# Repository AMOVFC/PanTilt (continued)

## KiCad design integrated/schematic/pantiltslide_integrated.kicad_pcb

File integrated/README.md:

# Integrated Controller — All Components Soldered (PCBWay assembly)

Fully-integrated version of the [4-axis final rig](../pantiltslide/pantiltslide_full.kicad_sch): every IC soldered directly to the board instead of socketed breakout modules, sized for a PCBWay turnkey assembly order. Companion to `pantiltslide/pantiltslide_full.kicad_sch` (the carrier-board version) — that board still exists and is untouched.

**Status: schematic + PCB placement complete and verified. Not routed, so not yet ready for fab.** See "PCB status" below.

## What's integrated vs. what stays a connector

| Was a socket/module in the carrier board | Now | Why |
|---|---|---|
| ESP32-S3 DevKitC (22-pin sockets) | ESP32-S3-WROOM-1-N16R8 module, soldered | Module has its own certified antenna/crystal — no RF layout risk |
| 4× TMC2209 stepstick sockets | 4× TMC2209-LA (QFN28), full app circuit | Standard Trinamic reference design, verified against datasheet |
| 2× AS5600 breakout connectors | Still connectors — now 4-pin JST XH (`J7`, `J8`) | An AS5600 needs a <3 mm air gap to a magnet on the rotating shaft, so it can't sit on the controller board. Off-the-shelf AS5600 breakout modules stay at the pan/tilt joints, wired back over XH. |
| TCA9548A breakout connector | TCA9548A (TSSOP24), soldered | Standard I2C mux app circuit |
| — (no regulation existed) | 24V→5V buck (LM2596S-5) → 5V→3.3V LDO (AMS1117-3.3) | Carrier board had no onboard regulation at all — this is genuinely new |
| — | USB-C connector, native USB on the S3 | Bench programming/power without the 24V rail connected |
| SSD1306 OLED connector | **Unchanged** — still a connector | It's a glass panel, not something an assembly house places |
| Motor/encoder/limit-switch connectors | Still connectors, now **JST XH** | Polarised and latching — see the Connectors table below |

All part choices (TMC2209-LA, ESP32-S3-WROOM-1, AS5600, TCA9548APWR, LM2596S-5, AMS1117-3.3) are mainstream, high-volume parts — good candidates for PCBWay's turnkey sourcing, not exotic.

## Pin map

Identical to the final rig's — see the main [README pin map](../README.md#pin-map). This schematic was built directly from that table, not from the carrier board's connectors (which had drifted: J33–J36 in the carrier board are leftover keyframe-button connectors that don't correspond to anything in the current firmware's pin map or the "trigger a shot over serial" design described in the main README. They're intentionally not carried over here.)

## Verification status

**ERC: 0 violations. Netlist verified pin-by-pin against the intended design.**

Nets use **global labels**, matching the convention in `pantiltslide_full.kicad_sch`.

### Sheet organisation

Drawn on an A1 sheet in four labelled blocks — power in / regulation, MCU + USB, I2C mux + off-board connectors, and the four TMC2209 drivers in a 2x2 grid.

Power rails are drawn as **GND / +3V3 / +5V / +24V symbols**, not text labels. 158 of the 331 net connections on this sheet are power (90 of them GND alone); as labels they buried the actual signal flow in a wall of repeated text. Only real signals carry label text now — 173 labels instead of 331.

### What was wrong in the first two drafts, and the actual root cause

KiCad **negates Y** when it places a library symbol: a pin at library coordinate `(lx, ly)` lands at screen `(sym_x + lx, sym_y − ly)`. The generator was *adding* `ly`, which mirrors every symbol vertically. Consequences:

- On vertically symmetric parts (resistors, capacitors) the label still landed on a real pin — but **the wrong one**, silently swapping pin 1 and pin 2.
- On asymmetric ICs (TMC2209, TCA9548A, ESP32-S3, USB-C) labels landed in empty space, so those pins read as unconnected.

I had earlier blamed this on `kicad-cli` being buggy. That was wrong — it was this bug, and the tool was reporting it accurately. Ground truth was confirmed from this repo's own `pantiltslide_full.kicad_sch`: J21 placed at `(430,40)` has pin 1 at `y=37.46` (`40 − 2.54`) and pin 4 at `y=45.08` (`40 − (−5.08)`).

Also fixed along the way:
- Net labels had no wire attaching them to pins (label-on-pin is not a connection mechanism in KiCad) — every pin now has a real drawn wire stub to its label.
- Everything snapped to the 1.27 mm connection grid.
- **USB-C `B6`/`B7` were left unconnected.** These are *not* redundant stacked pins — D+ and D− appear on both sides of a Type-C connector so the plug works either way up. Tying only the A-side would have produced a port that works in one orientation and is dead when flipped. `A6+B6` and `A7+B7` are now tied.

### How it was verified

- `kicad-cli sch erc` → **0 violations**.
- Netlist exported and diffed against the intended design: **75/80 nets byte-identical**. The 5 differences were each confirmed benign — `#PWR`/`#FLG` symbols are virtual and by design never exported as components, and the USB-C `A12/B1/B12` (GND) and `A9/B4/B9` (VBUS) pads share exact coordinates with `A1`/`A4`, so KiCad correctly folds them into those nets.
- Spot-checked against the firmware pin map: `GPIO4 → U4.STEP`, `GPIO10 →` all four driver `EN` pins, `TMC_UART` = 1 kΩ series resistor + `IO41` + all four `PDN_UART` pins, `I2C_PAN_SDA` = pull-up + mux channel 0 + AS5600 `SDA`.

The two hand-authored symbols (AS5600, ESP32-S3-WROOM-1) ship as an editable `New_Library.kicad_sym` with a `sym-lib-table`, so they open normally in the Symbol Editor rather than existing only as embedded copies.

Layout still needs a human pass — see "PCB status" below.

## PCB status

One board: `schematic/pantiltslide_integrated.*`

| | |
|---|---|
| Size | 150 × 120 mm |
| Layers | 4 (F.Cu / GND / 3V3 / B.Cu) |
| Footprints | 80 |
| ERC | **0** |
| Schematic parity | **0** |
| DRC (excl. routing) | 7 (4 cosmetic silk, 2 antenna-overhang silk, 1 benign keepout layer-set) |
| **Routing** | **not routed — 253 ratsnest connections** |

**The board is placed and netted, not routed.** Every pad carries its correct net so the ratsnest is complete and correct, but no copper tracks exist yet. Routing is the next step — either by hand in KiCad, or by exporting Specctra DSN (File → Export → Specctra DSN, GUI only — `kicad-cli` has no DSN export) and running Freerouting.

## Connectors

Everything that leaves the board is **JST XH** — polarised so a harness can't be plugged in backwards, latching so it won't shake loose on a moving rig, and rated 3 A/contact (comfortably above the TMC2209's 2 A RMS ceiling). The sole exception is the 24 V input, which keeps a screw terminal for bare supply leads.

| Ref | Function | Connector |
|---|---|---|
| `J1` | 24 V motor supply in | **Screw terminal**, 5.0 mm |
| `J2` | USB-C (power + programming) | USB-C receptacle |
| `J3`–`J6` | Motors: slide / pan / tilt / Z | XH 4-pin |
| `J7`, `J8` | AS5600 modules: pan / tilt | XH 4-pin — `3V3, GND, SDA, SCL` |
| `J9` | SSD1306 OLED | XH 4-pin — `3V3, GND, SDA, SCL` |
| `J10`, `J11` | Encoders: jog / angle | XH 4-pin — `A, B, push, GND` |
| `J12`–`J14` | Limit switches: slide min / max / Z home | XH 2-pin |

Every connector prints its **function on the front silkscreen** (`Motor_Tilt`, `AS5600_Pan`, `Limit_Z_Home` …) directly below its reference designator, so the board can be wired without the schematic to hand. pcbnew's default leaves the Value field hidden and on `F.Fab`, which is a documentation layer and never reaches the physical board — both were changed for all 14 connectors, and the placement packer reserves vertical room for the two text rows.

The AS5600s are **off-the-shelf breakout modules** mounted at the pan and tilt joints, not parts on this board — the sensor has to sit within a few mm of a diametrically-magnetised magnet on the rotating shaft. Two things to check on whichever module you buy:

- **Pin order.** `J7`/`J8` are wired `1=3V3, 2=GND, 3=SDA, 4=SCL`. Most AS5600 breakouts use that order, but confirm before crimping — a swapped 3V3/GND will destroy the module.
- **The `DIR` pin.** On the bare IC, `DIR` sets count direction and must not float. Most breakouts tie it low or provide a jumper; if yours leaves it floating, ground it, or pan/tilt direction will be indeterminate.

Placement is programmatic: components are clustered by subsystem with guaranteed non-overlapping courtyards, but it is not hand-optimised. **Expect to move things before routing**, particularly:

- The 24 V switching node around `U1`/`L1`/`D1` wants tight loop area — keep `C1`/`C2` right at the regulator.
- Each TMC2209's `C_VS` bulk cap should sit hard against its `VS` pin.
- Sense resistors want a short, dedicated return to the driver's GND pad.

### Deliberate PCB decisions

- **ESP32 module overhangs the top edge.** Its footprint carries a 21 mm antenna keepout; letting it hang off the edge keeps the antenna clear instead of sterilising 21 mm of interior copper. The keepout is present on all four copper layers in the board file.
- **4 layers**, with In1 a solid ground plane directly under the signal layers — chosen because four switching stepper drivers, a 24 V buck, and an RF module on one board make return-path integrity the dominant risk.
- **Design rules live in the `.kicad_pro`**, set to PCBWay's standard process (0.15 mm track/clearance, 0.2 mm min hole, 0.45/0.13 mm vias). This matters: KiCad reads DRC constraints from the *project* file, not the `.kicad_pcb`, so limits set only on the board object are ignored at DRC time.
- **Every bypass cap is WIRED to the pin it serves**, not hung on a shared rail symbol. A cap drawn as `+24V -> cap -> GND` is electrically right but tells layout nothing, since all 26 look identical; drawing its rail side onto the chip's own supply pin makes the association part of the schematic and impossible to lose. The GND side still uses a GND symbol (ground is a plane, not a routed net). This is a drawing change only -- the netlist is byte-identical, verified by diffing before/after: **0 pins changed nets**.
- **Every bypass cap also carries a `Decouples` field** naming the pin it serves (`C15` -> `U4 +24V`). A rail-to-GND cap is indistinguishable from every other one in the netlist, so without this a layout pass has no way to know `C15` belongs beside `U4` rather than `U7`. The field is hidden and on `F.Fab` -- it is metadata, not silkscreen. `tools/check_decoupling.py` re-measures every cap's distance to its owner and flags anything over 10mm; run it after any placement change.
- **Zones are defined but unfilled.** `pcbnew`'s zone filler segfaults outside the GUI; KiCad fills them on open, or press `B`.

### Remaining DRC items (all benign)

- `lib_footprint_mismatch` on the ESP32 — the library defines its keepout across all 32 possible copper layers and KiCad correctly trims it to this board's 4. Not a defect.
- `silk_edge_clearance` — the ESP32's silk outline crosses the edge it deliberately overhangs.
- `silk_overlap` / `silk_over_copper` — cosmetic; normal silkscreen cleanup during layout.

## Reproducing / regenerating

This board is generated, not hand-drawn. `tools/run_all.py` rebuilds everything from source:

```bash
python integrated/tools/run_all.py
```

`gen_sch.py` builds the schematic, `export_design.py` dumps the netlist (taken from KiCad's own netlist export, so the PCB can never disagree with the schematic), `build_pcb.py` builds the board via the `pcbnew` Python API, and `write_pro.py` writes the design rules. Editing by hand in KiCad from here on is fine — the generators were scaffolding, not a pipeline you have to keep using.

## Before ordering

- **Route the board.** Nothing is routed yet.
- The TMC2209 sense resistors are `0.11 Ω` placeholders matching the firmware's `tmc::R_SENSE_OHMS`; confirm against the parts actually ordered.
- Fuse rating (`2 A`) is a placeholder — size it to your motor supply.
- The board ships a `sym-lib-table` pointing at a shared `New_Library.kicad_sym` (AS5600 + ESP32-S3-WROOM-1). If you move folders, that relative path needs updating.

## Verified against

- TMC2209: Analog Devices datasheet rev 1.09 (charge pump caps, sense resistors, VREF/SPREAD/CLK strapping, MS1/MS2 address table — matches the existing project's own table)
- ESP32-S3-WROOM-1: Espressif module datasheet (full pin table cross-checked pin-by-pin against the firmware's GPIO map)
- AS5600: ams-OSRAM datasheet (confirmed SOIC-8, not the SOT23-6 I originally assumed — corrected before drawing anything)
- All footprints confirmed present in the local KiCad 9.0 install before use

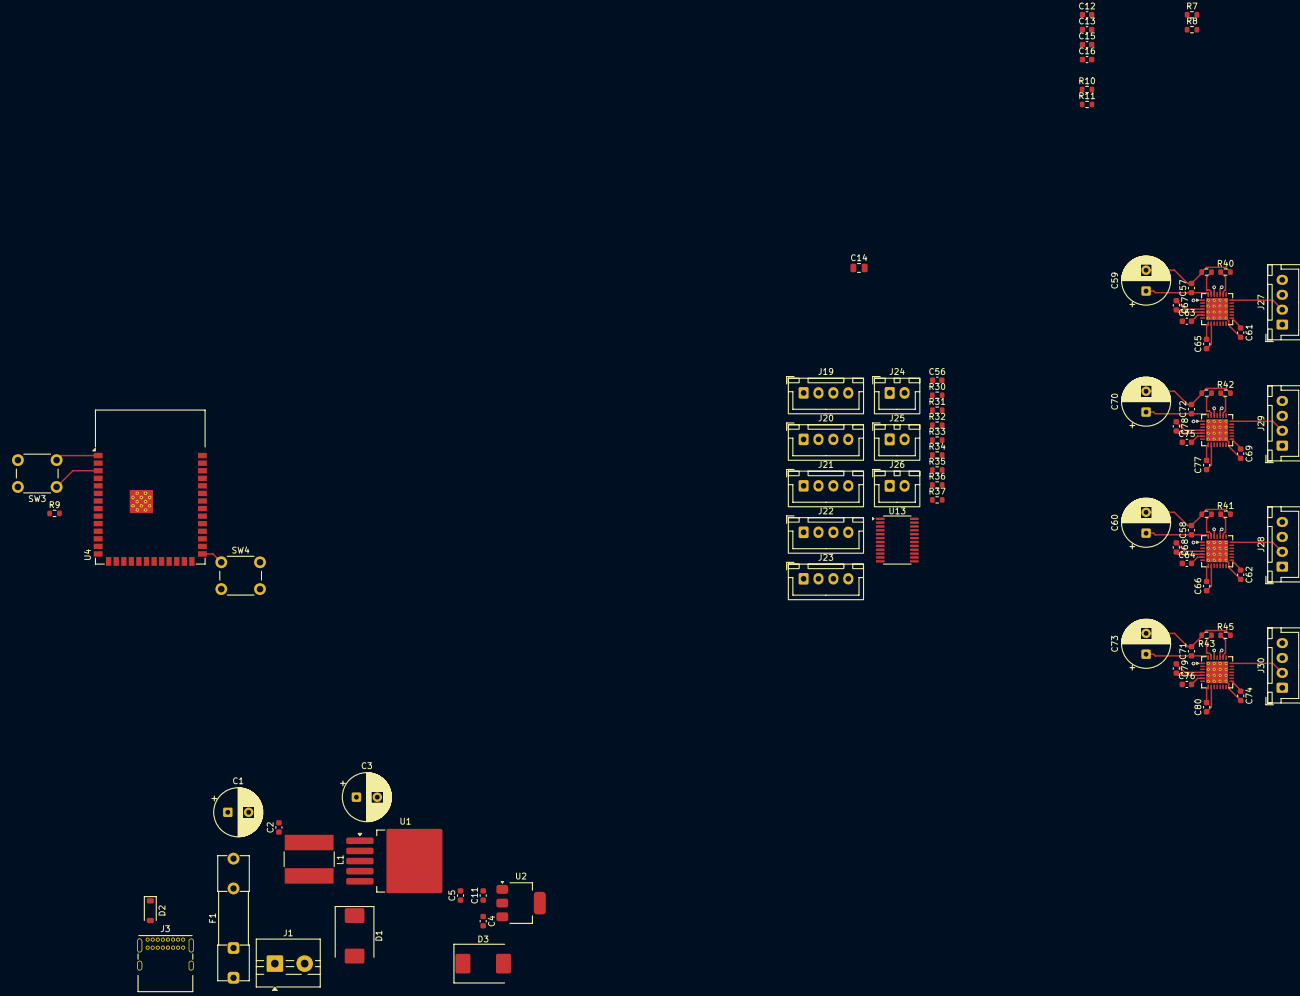
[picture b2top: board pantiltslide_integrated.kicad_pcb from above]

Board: 4 copper layers, 86 parts (0 on the bottom side), 74 nets.

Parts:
C1, C59, C60, C73: 100uF_35V; CP_Radial_D8.0mm_P3.50mm
C2, C13, C15, C16, C56, C57, C58, C61, C62, C63, C64, C69, C71, C74, C75, C76: 100nF; C_0603_1608Metric
C3: 220uF_25V; CP_Radial_D8.0mm_P3.50mm
C4: 10uF; C_0603_1608Metric
C5: 0.1uF; C_0603_1608Metric
C11: 22uF; C_0603_1608Metric
C12: 1uF; C_0603_1608Metric
C14: 10uF; C_0805_2012Metric
C65, C66, C77, C80: 4.7uF; C_0603_1608Metric
C67, C68, C78, C79: 22nF; C_0603_1608Metric
C70: 100nF; CP_Radial_D8.0mm_P3.50mm
C72: 100uF_35V; C_0603_1608Metric
D1, D3: SS34; D_SMC
D2: SS14; D_SOD-123
F1: 2A; Fuseholder_Clip-5x20mm_Littelfuse_111_Inline_P20.00x5.00mm_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
J1: 24V_In; TerminalBlock_MaiXu_MX126-5.0-02P_1x02_P5.00mm
J3: USB_PROG; USB_C_Receptacle_GCT_USB4085
J19: AS5600_Pan; JST_XH_B4B-XH-A_1x04_P2.50mm_Vertical
J20: AS5600_Tilt; JST_XH_B4B-XH-A_1x04_P2.50mm_Vertical
J21: OLED; JST_XH_B4B-XH-A_1x04_P2.50mm_Vertical
J22: Enc_Jog; JST_XH_B4B-XH-A_1x04_P2.50mm_Vertical
J23: Enc_Angle; JST_XH_B4B-XH-A_1x04_P2.50mm_Vertical
J24: Limit_Min; JST_XH_B2B-XH-A_1x02_P2.50mm_Vertical
J25: Limit_Max; JST_XH_B2B-XH-A_1x02_P2.50mm_Vertical
J26: Limit_Z_Home; JST_XH_B2B-XH-A_1x02_P2.50mm_Vertical
J27: Motor_Slide; JST_XH_B4B-XH-A_1x04_P2.50mm_Vertical
J28: Motor_Tilt; JST_XH_B4B-XH-A_1x04_P2.50mm_Vertical
J29: Motor_Pan; JST_XH_B4B-XH-A_1x04_P2.50mm_Vertical
J30: Motor_Z; JST_XH_B4B-XH-A_1x04_P2.50mm_Vertical
L1: 100uH; L_Bourns-SRN8040_8x8.15mm
R7, R8: 5.1k; R_0603_1608Metric
R9, R11: 10k; R_0603_1608Metric
R10: 1k; R_0603_1608Metric
R30, R31, R32, R33, R34, R35, R36, R37: 4.7k; R_0603_1608Metric
R38, R39, R40, R41, R42, R43, R44, R45: 0.11; R_0603_1608Metric
SW3: RESET; SW_PUSH_6mm
SW4: BOOT; SW_PUSH_6mm
U1: LM2596S-5; TO-263-5_TabPin3
U2: AMS1117-3.3; SOT-223-3_TabPin2
U4: ESP32-S3-WROOM-1-N16R8; ESP32-S3-WROOM-1
U13: TCA9548APWR; TSSOP-24_4.4x7.8mm_P0.65mm
U14, U15, U16, U17: TMC2209-LA; VQFN-28-1EP_5x5mm_P0.5mm_EP3.7x3.7mm_ThermalVias

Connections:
+3V3: C5.1, C11.1, C13.1, C14.1, C15.1, C16.1, C56.1, C61.1, C62.1, C69.1, C74.1, J19.1, J20.1, J21.1, R9.2, R11.2, R30.2, R31.2, R32.2, R33.2, R34.2, R35.2, R36.2, R37.2, U2.2 (VO), U4.2 (3V3), U13.3 (~RESET), U13.24 (VCC), U14.15 (VCC_IO), U15.10 (MS2/AD1), U15.15 (VCC_IO), U16.9 (MS1/AD0), U16.15 (VCC_IO), U17.9 (MS1/AD0), U17.10 (MS2/AD1), U17.15 (VCC_IO)
+5V: C3.1, C4.1, D2.1 (K), L1.1, U1.4 (FB), U2.3 (VI)
+24V: C1.1, C2.1, C57.1, C58.1, C59.1, C60.1, C63.1, C64.1, C70.1, C71.1, C72.1, C73.1, C75.1, C76.1, F1.2, U1.1 (VIN), U14.22 (VS), U14.28 (VS), U15.22 (VS), U15.28 (VS), U16.22 (VS), U16.28 (VS), U17.22 (VS), U17.28 (VS)
/power/+24V_RAW: F1.1, J1.1
/power/SW_NODE: D1.1 (K), L1.2, U1.2 (OUT)
/stepper drivers/EN: U14.2 (~EN), U15.2 (~EN), U16.2 (~EN), U17.2 (~EN)
/stepper drivers/M0_A1: J27.1, U14.24 (OA1)
/stepper drivers/M0_A2: J27.2, U14.21 (OA2)
/stepper drivers/M0_B1: J27.3, U14.26 (OB1)
/stepper drivers/M0_B2: J27.4, U14.1 (OB2)
/stepper drivers/M1_A1: J29.1, U16.24 (OA1)
/stepper drivers/M1_A2: J29.2, U16.21 (OA2)
/stepper drivers/M1_B1: J29.3, U16.26 (OB1)
/stepper drivers/M1_B2: J29.4, U16.1 (OB2)
/stepper drivers/M2_A1: J28.1, U15.24 (OA1)
/stepper drivers/M2_A2: J28.2, U15.21 (OA2)
/stepper drivers/M2_B1: J28.3, U15.26 (OB1)
/stepper drivers/M2_B2: J28.4, U15.1 (OB2)
/stepper drivers/M3_A1: J30.1, U17.24 (OA1)
/stepper drivers/M3_A2: J30.2, U17.21 (OA2)
/stepper drivers/M3_B1: J30.3, U17.26 (OB1)
/stepper drivers/M3_B2: J30.4, U17.1 (OB2)
/stepper drivers/UART: U14.14 (~PD/UART), U15.14 (~PD/UART), U16.14 (~PD/UART), U17.14 (~PD/UART)
EN_ESP: C12.1, R9.1, SW3.1, U4.3 (EN)
GND: C1.2, C2.2, C3.2, C4.2, C5.2, C11.2, C12.2, C13.2, C14.2, C15.2, C16.2, C56.2, C57.2, C58.2, C59.2, C60.2, C61.2, C62.2, C65.1, C66.2, C69.2, C70.2, C71.2, C72.2, C73.2, C74.2, C77.1, C80.1, D1.2 (A), D3.1 (K), J1.2, J3.A1 (GND), J3.A12 (GND), J3.B1 (GND), J3.B12 (GND), J19.2, J20.2, J21.2, J22.4, J23.4, J24.2, J25.2, J26.2, R7.2, R8.2, R38.2, R39.2, R40.2, R41.2, R42.2, R43.2, R44.2, R45.2, SW3.2, SW4.2, U1.3 (GND), U1.5 (~ON/OFF), U2.1 (GND), U4.1 (GND), U4.40 (GND), U4.41 (GND), U13.1 (A0), U13.2 (A1), U13.12 (GND), U13.21 (A2), U14.3 (GND), U14.7 (SPREAD), U14.9 (MS1/AD0), U14.10 (MS2/AD1), U14.13 (CLK), U14.18 (GND), U14.20 (STDBY), U14.29 (GND), U15.3 (GND), U15.7 (SPREAD), U15.9 (MS1/AD0), U15.13 (CLK), U15.18 (GND), U15.20 (STDBY), U15.29 (GND), U16.3 (GND), U16.7 (SPREAD), U16.10 (MS2/AD1), U16.13 (CLK), U16.18 (GND), U16.20 (STDBY), U16.29 (GND), U17.3 (GND), U17.7 (SPREAD), U17.13 (CLK), U17.18 (GND), U17.20 (STDBY), U17.29 (GND)
GPIO0: R11.1, SW4.1, U4.27 (IO0)
GPIO11: R30.1, U4.19 (IO11), U13.23 (SDA)
GPIO12: R34.1, U4.20 (IO12), U13.22 (SCL)
GPIO13: J21.3, R33.1, U4.21 (IO13)
GPIO14: J21.4, R37.1, U4.22 (IO14)
GPIO15: J22.1, U4.8 (IO15)
GPIO16: J22.2, U4.9 (IO16)
GPIO17: J22.3, U4.10 (IO17)
GPIO18: J23.1, U4.11 (IO18)
GPIO19: J3.A7 (D-), J3.B7 (D-), U4.13 (IO19)
GPIO20: J3.A6 (D+), J3.B6 (D+), U4.14 (IO20)
GPIO21: J23.2, U4.23 (IO21)
GPIO38: J23.3, U4.31 (IO38)
GPIO39: J24.1, U4.32 (IO39)
GPIO40: J25.1, U4.33 (IO40)
GPIO42: J26.1, U4.35 (IO42)
GPIO47: R10.1, U4.24 (IO47)
I2C_PAN_SCL: J19.4, R35.1, U13.5 (SC0)
I2C_PAN_SDA: J19.3, R31.1, U13.4 (SD0)
I2C_TILT_SCL: J20.4, R36.1, U13.7 (SC1)
I2C_TILT_SDA: J20.3, R32.1, U13.6 (SD1)
unnamed: C65.2, U14.8 (5VOUT)
unnamed: R40.1, U14.23 (BRA)
unnamed: R38.1, U14.27 (BRB)
unnamed: C67.2, U14.5 (CPI)
unnamed: C67.1, U14.4 (CPO)
unnamed: C63.2, U14.6 (VCP)
unnamed: C66.1, U15.8 (5VOUT)
unnamed: R41.1, U15.23 (BRA)
unnamed: R39.1, U15.27 (BRB)
unnamed: C68.2, U15.5 (CPI)
unnamed: C68.1, U15.4 (CPO)
unnamed: C64.2, U15.6 (VCP)
unnamed: C77.2, U16.8 (5VOUT)
unnamed: R44.1, U16.23 (BRA)
unnamed: R42.1, U16.27 (BRB)
unnamed: C78.2, U16.5 (CPI)
unnamed: C78.1, U16.4 (CPO)
unnamed: C75.2, U16.6 (VCP)
unnamed: C80.2, U17.8 (5VOUT)
unnamed: R45.1, U17.23 (BRA)
unnamed: R43.1, U17.27 (BRB)
unnamed: C79.2, U17.5 (CPI)
unnamed: C79.1, U17.4 (CPO)
unnamed: C76.2, U17.6 (VCP)
TMC_UART: R10.2, U4.34 (IO41)
USBCC1: J3.A5 (CC1), R7.1
USBCC2: J3.B5 (CC2), R8.1
USB_VBUS: D2.2 (A), J3.A4 (VBUS), J3.A9 (VBUS), J3.B4 (VBUS), J3.B9 (VBUS)

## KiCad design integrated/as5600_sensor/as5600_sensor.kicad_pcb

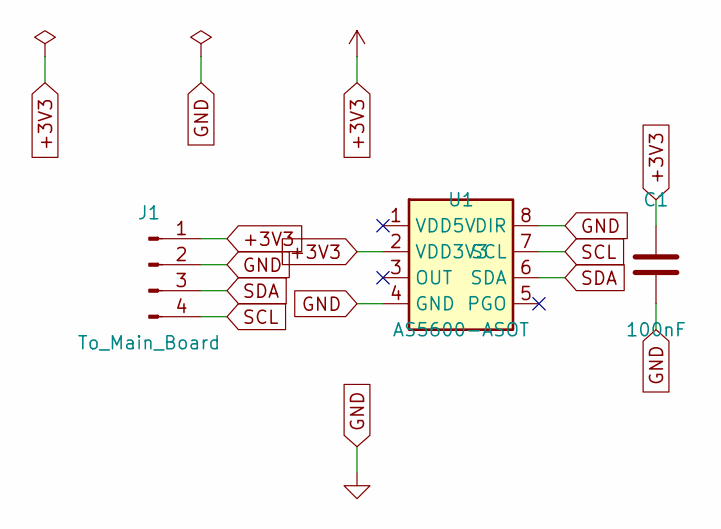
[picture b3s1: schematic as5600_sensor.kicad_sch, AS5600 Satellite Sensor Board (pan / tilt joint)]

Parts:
C1: 100nF; C_0603_1608Metric
J1: To_Main_Board; PinHeader_1x04_P2.54mm_Vertical
U1: AS5600-ASOT; SOIC-8_3.9x4.9mm_P1.27mm

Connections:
+3V3: C1.1, J1.1, U1.2 (VDD3V3)
GND: C1.2, J1.2, U1.4 (GND), U1.8 (DIR)
SCL: J1.4, U1.7 (SCL)
SDA: J1.3, U1.6 (SDA)

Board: 2 copper layers, 5 parts (0 on the bottom side), 4 nets, no tracks yet.

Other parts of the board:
H1, H2: MountingHole_2.2mm_M2

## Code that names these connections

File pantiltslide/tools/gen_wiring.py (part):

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#   sheet_y = origin_y - local_y      <-- Y IS INVERTED (.kicad_sym is Y-up,
#                                         .kicad_sch is Y-down)
# Ground truth: J1 (Conn_01x22_Socket) at origin y=104.14, pin4 local y=17.78,
# and KiCad placed that pin's GPIO_4 label at y=86.36 == 104.14 - 17.78.
# ---------------------------------------------------------------------------

def sheet_pos(cx, cy, lx, ly):
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# All four drivers share one half-duplex UART bus. On the SilentStepStick the
# chip's single PDN_UART pin is broken out twice: header pin 12 ("UART") via an
# onboard 1k series resistor, and header pin 11 ("PDN") directly.
TMC_TX_NET = "GPIO_41"   # ESP32 TX -> pin 12 UART (through module's 1k)
TMC_RX_NET = "GPIO_42"   # ESP32 RX <- pin 11 PDN  (direct)

# With UART in use MS1/MS2 stop selecting microstepping and become the slave
# address (MS1 = bit0, MS2 = bit1). Strapped on-board so a kit builder has
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           9: dirn, 10: step,
           11: TMC_RX_NET, 12: TMC_TX_NET,
           14: ms2, 15: ms1,
           16: "GPIO_10"},
          TMC_NC, TMC_REF_DY, TMC_VAL_DY)

def add_c4(ref, x, y, value, desc, nets, nc=()):
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# ===========================================================================

#                                                                                    addr  MS1     MS2
add_tmc("U1", 290, 40,  "GPIO_4",  "GPIO_5",  "SLIDE_M1A", "SLIDE_M1B", "SLIDE_M2A", "SLIDE_M2B", "GND",  "GND")   # 0
add_tmc("U2", 290, 115, "GPIO_6",  "GPIO_7",  "PAN_M1A",   "PAN_M1B",   "PAN_M2A",   "PAN_M2B",   "3.3v", "GND")   # 1
add_tmc("U3", 290, 190, "GPIO_8",  "GPIO_9",  "TILT_M1A",  "TILT_M1B",  "TILT_M2A",  "TILT_M2B",  "GND",  "3.3v")  # 2
add_tmc("U4", 290, 265, "GPIO_47", "GPIO_48", "AUX_M1A",   "AUX_M1B",   "AUX_M2A",   "AUX_M2B",   "3.3v", "3.3v")  # 3

add_c4("J17", 360, 40,  "Motor_Slide", "NEMA17 slide motor, 4-wire",
       {1: "SLIDE_M1A", 2: "SLIDE_M1B", 3: "SLIDE_M2A", 4: "SLIDE_M2B"})
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add_c4("J22", 430, 80,  "AS5600_Tilt", "AS5600 magnetic angle sensor, tilt axis (via TCA9548A ch1)",
       {1: "3.3v", 2: "GND", 3: "MUX_CH1_SDA", 4: "MUX_CH1_SCL"})
add_c4("J23", 430, 120, "OLED", "SSD1306 OLED status display, isolated I2C bus B",
       {1: "3.3v", 2: "GND", 3: "GPIO_13", 4: "GPIO_14"})

# One manual control encoder per axis. Pin 4 is left as a no-connect so the
# encoder's push switch can be brought in later without a board change.
add_c4("J29", 430, 170, "Enc_Slide", "Slide-axis manual control encoder (A/B quadrature, common to GND)",
       {1: "GPIO_15", 2: "GPIO_16", 3: "GND"}, nc=(4,))
add_c4("J30", 430, 210, "Enc_Pan", "Pan-axis manual control encoder (A/B quadrature, common to GND)",
       {1: "GPIO_17", 2: "GPIO_18", 3: "GND"}, nc=(4,))
add_c4("J31", 430, 250, "Enc_Tilt", "Tilt-axis manual control encoder (A/B quadrature, common to GND)",
       {1: "GPIO_21", 2: "GPIO_38", 3: "GND"}, nc=(4,))
add_c4("J32", 430, 290, "Enc_Aux", "4th-axis manual control encoder (A/B quadrature, common to GND)",
       {1: "GPIO_19", 2: "GPIO_20", 3: "GND"}, nc=(4,))

add_c8("J20", 520, 40,  "TCA9548A_Mux", "TCA9548A 8-ch I2C mux, ch0->pan AS5600, ch1->tilt AS5600",
       {1: "3.3v", 2: "GND", 3: "GPIO_11", 4: "GPIO_12", 5: "MUX_CH0_SDA", 6: "MUX_CH0_SCL",
        7: "MUX_CH1_SDA", 8: "MUX_CH1_SCL"})

add_st2("J26", 520, 120, "Limit_Min", "Slide axis min-travel limit switch, idle HIGH / triggered LOW",
        {1: "GPIO_39", 2: "GND"})
add_st2("J27", 520, 160, "Limit_Max", "Slide axis max-travel limit switch, idle HIGH / triggered LOW",
        {1: "GPIO_40", 2: "GND"})

# Keyframe/transport buttons -- one named terminal each so the schematic says
# which button is which, rather than leaving a bare GPIO number for a kit
# builder to guess at. All active-LOW to GND on the ESP32's internal pull-ups,
# so no external resistors are needed.
#
# GPIO_45/46 are strapping pins that must read LOW at reset. A button-to-GND is
# safe on both: their default state is an internal pull-down (already LOW), and
# holding one down during power-up only reinforces that same required LOW.
BTN_DESC = "%s pushbutton, active-low to GND (enable the internal pull-up in firmware)"
add_st2("J33", 520, 210, "Btn_SetKeyframe",   BTN_DESC % "Set keyframe",
        {1: "GPIO_1", 2: "GND"})
add_st2("J34", 520, 245, "Btn_ClearKeyframe", BTN_DESC % "Delete/clear keyframe",
        {1: "GPIO_3", 2: "GND"})
add_st2("J35", 520, 280, "Btn_PlayPause",     BTN_DESC % "Play/pause",
        {1: "GPIO_45", 2: "GND"})
add_st2("J36", 520, 315, "Btn_Reset",         BTN_DESC % "Reset",
        {1: "GPIO_46", 2: "GND"})

_OUT = os.path.join(os.path.dirname(os.path.abspath(__file__)), '_body.generated.txt')
with open(_OUT, 'w', encoding='utf-8') as f:
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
